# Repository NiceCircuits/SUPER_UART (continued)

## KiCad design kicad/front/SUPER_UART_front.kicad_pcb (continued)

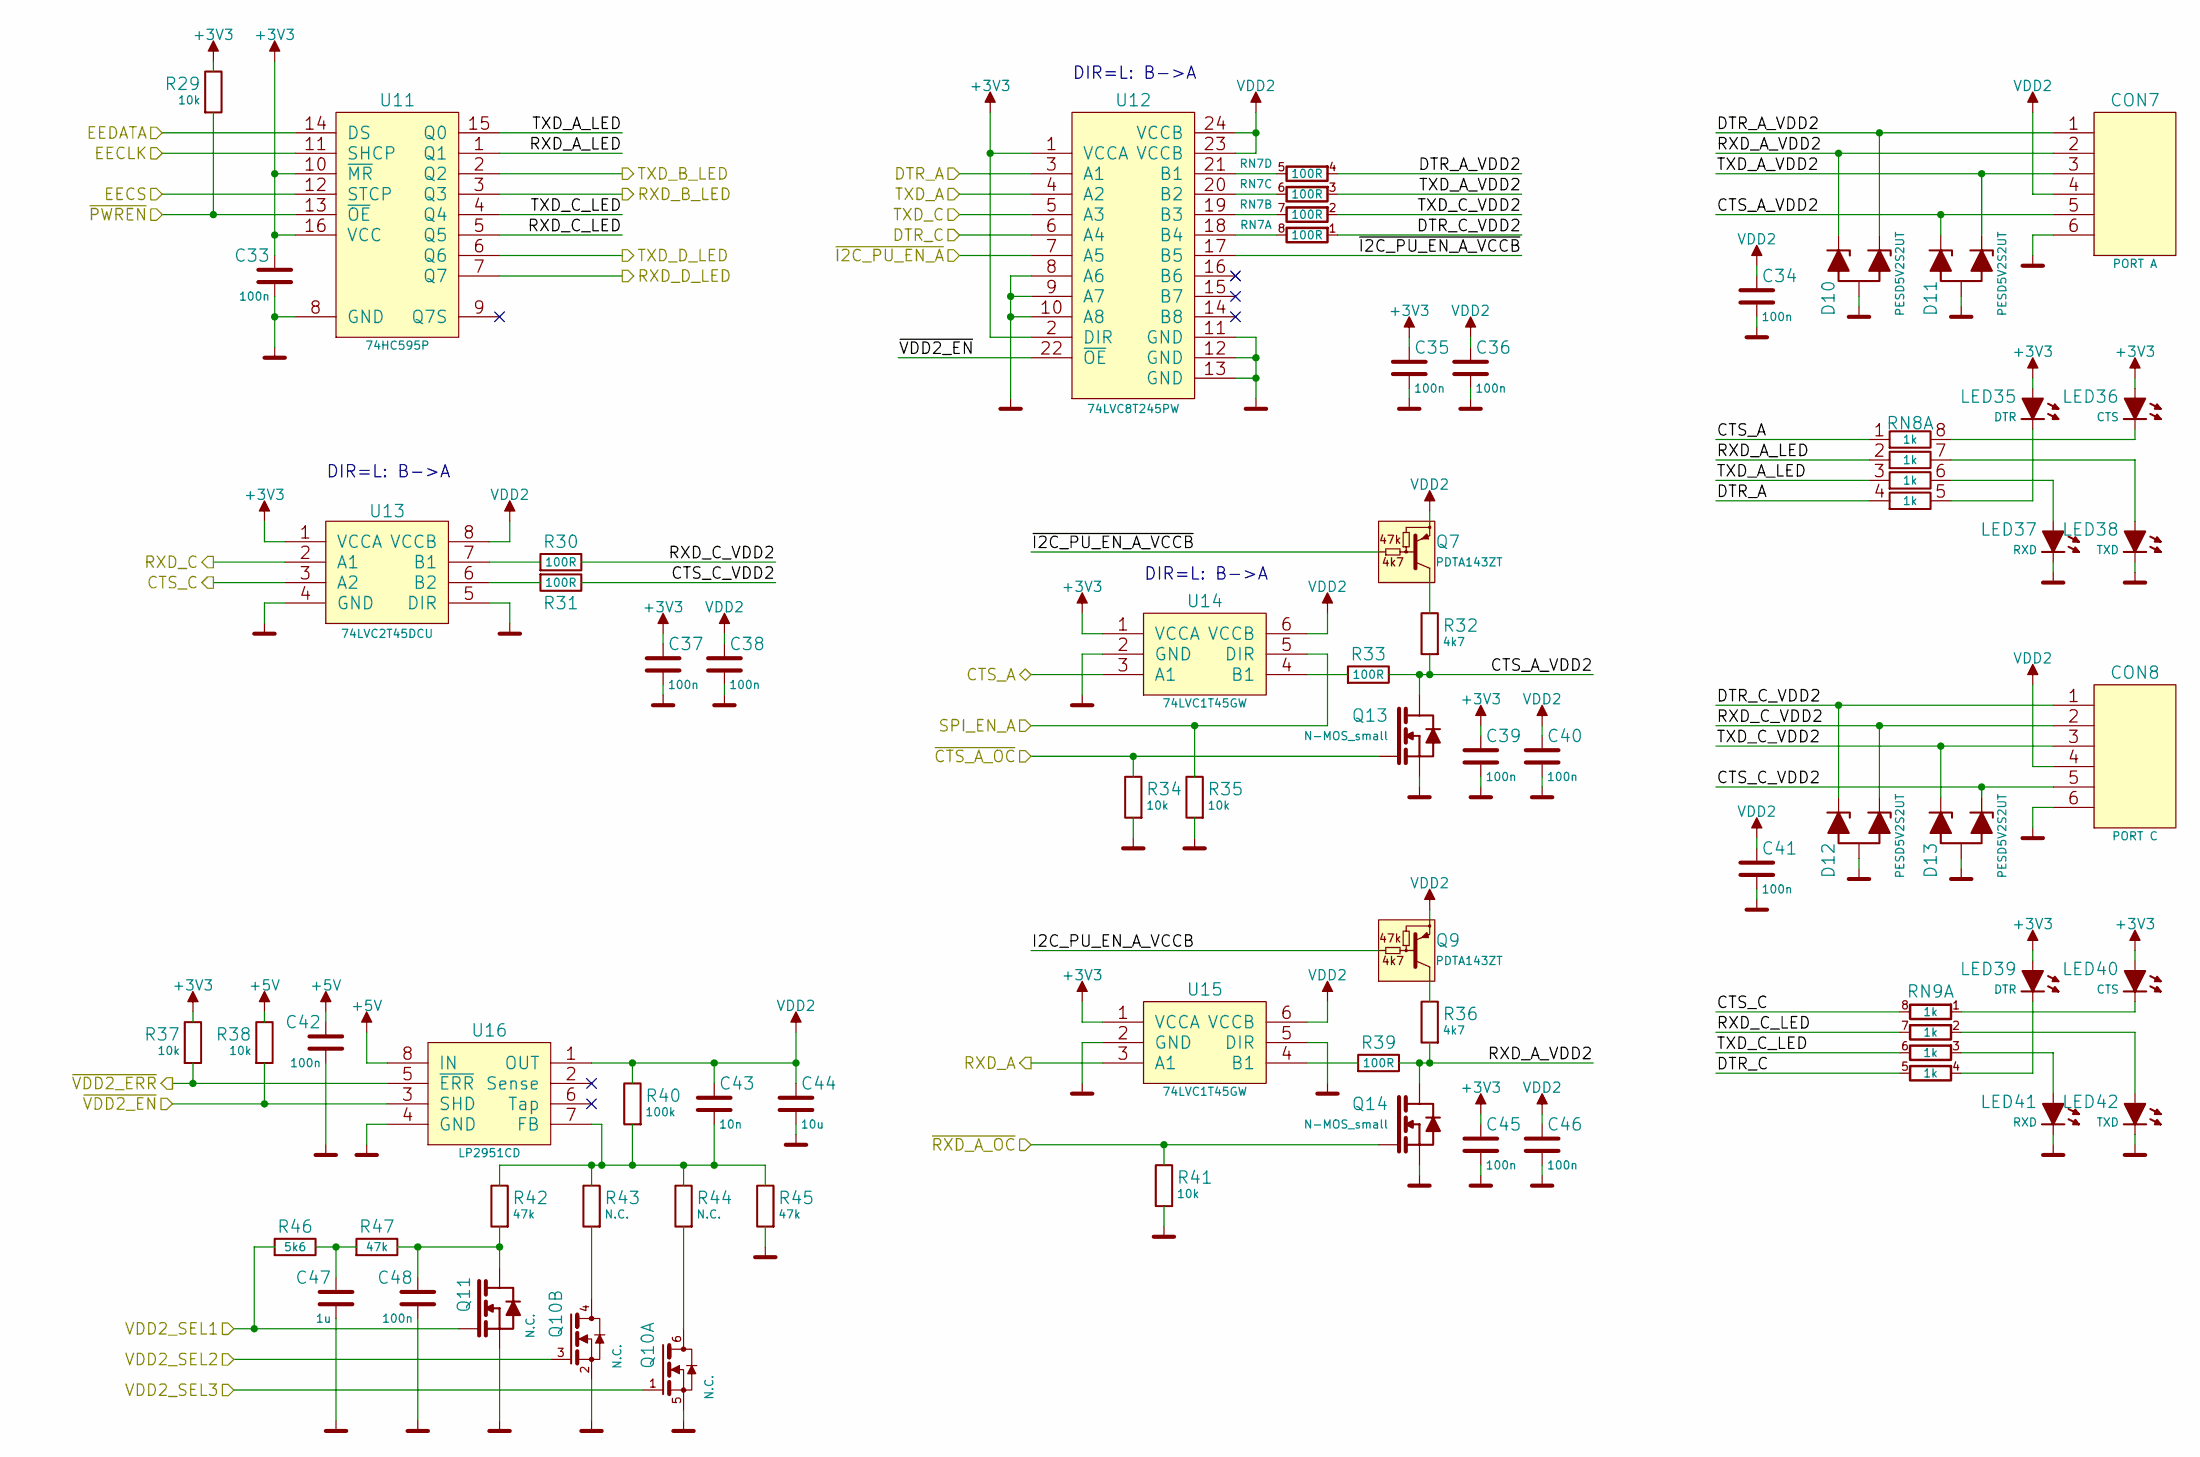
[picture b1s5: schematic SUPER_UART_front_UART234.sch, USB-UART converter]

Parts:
C33, C34, C35, C36, C37, C38, C39, C40, C41, C42, C45, C46, C48: 100n; 0603_N
C43: 10n; 0603_N
C44: 10u; 0805_N
C47: 1u; 0603_N
CON7: PORT A; NIGINI_NCDW-06
CON8: PORT C; NIGINI_NCDW-06
D10, D11, D12, D13: PESD5V2S2UT; SOT23-3_N
LED35, LED39: DTR; 0805D
LED36, LED40: CTS; 0805D
LED37, LED41: RXD; 0805D
LED38, LED42: TXD; 0805D
Q7, Q9: PDTA143ZT; SOT23-3_N
Q10: N.C.; SC70-6_N
Q11: N.C.; SOT23-3_N
Q13, Q14: N-MOS_small; SOT23-3_N
R29, R34, R35, R37, R38, R41: 10k; 0603_R_N
R30, R31, R33, R39: 100R; 0603_R_N
R32, R36: 4k7; 0603_R_N
R40: 100k; 0603_R_N
R42, R45, R47: 47k; 0603_R_N
R43, R44: N.C.; 0603_R_N
R46: 5k6; 0603_R_N
RN7: 100R; 4x0603_N
RN8, RN9: 1k; 4x0603_N
U11: 74HC595P; TSSOP-16_N
U12: 74LVC8T245PW; TI_TSSOP-24_N
U13: 74LVC2T45DCU; TI_VSSOP-8_N
U14, U15: 74LVC1T45GW; SC70-6_N
U16: LP2951CD; SOIC-8_N

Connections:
+3V3: C33.1, C35.1, C37.1, C39.1, C45.1, LED35.2 (C), LED36.2 (C), LED39.2 (C), LED40.2 (C), R29.2, R37.2, U11.10 (~MR), U11.16 (VCC), U12.1 (VCCA), U12.2 (DIR), U13.1 (VCCA), U14.1 (VCCA), U15.1 (VCCA); also elsewhere on the board
+5V: C42.1, R38.2, U16.8 (IN); also elsewhere on the board
/CTS_A: RN8.1, U14.3 (A1); also elsewhere on the board
/CTS_C: RN9.8, U13.3 (A2); also elsewhere on the board
/DTR_A: RN8.4 (1), U12.3 (A1); also elsewhere on the board
/DTR_C: RN9.5, U12.6 (A4); also elsewhere on the board
/EECLK: U11.11 (SHCP); also elsewhere on the board
/EECS: U11.12 (STCP); also elsewhere on the board
/EEDATA: U11.14 (DS); also elsewhere on the board
/RXD_A: U15.3 (A1); also elsewhere on the board
/RXD_C: U13.2 (A1); also elsewhere on the board
/SUPER_UART_front_UART1/RXD_B_LED: U11.3 (Q3); also elsewhere on the board
/SUPER_UART_front_UART1/RXD_D_LED: U11.7 (Q7); also elsewhere on the board
/SUPER_UART_front_UART1/TXD_B_LED: U11.2 (Q2); also elsewhere on the board
/SUPER_UART_front_UART1/TXD_D_LED: U11.6 (Q6); also elsewhere on the board
/SUPER_UART_front_UART234/CTS_A_VDD2: CON7.5, D11.1 (C1), Q13.3 (D), R32.1, R33.2
/SUPER_UART_front_UART234/CTS_C_VDD2: CON8.5, D13.2 (C2), R31.2
/SUPER_UART_front_UART234/DTR_A_VDD2: CON7.1, D10.2 (C2), RN7.4
/SUPER_UART_front_UART234/DTR_C_VDD2: CON8.1, D12.1 (C1), RN7.1
/SUPER_UART_front_UART234/I2C_PU_EN_A: U12.7 (A5); also elsewhere on the board
/SUPER_UART_front_UART234/RXD_A_LED: RN8.2 (1), U11.1 (Q1)
/SUPER_UART_front_UART234/RXD_A_VDD2: CON7.2, D10.1 (C1), Q14.3 (D), R36.1, R39.2
/SUPER_UART_front_UART234/RXD_C_LED: RN9.7, U11.5 (Q5)
/SUPER_UART_front_UART234/RXD_C_VDD2: CON8.2, D12.2 (C2), R30.2
/SUPER_UART_front_UART234/SPI_EN_A: R35.2, U14.5 (DIR); also elsewhere on the board
/SUPER_UART_front_UART234/TXD_A_LED: RN8.3 (1), U11.15 (Q0)
/SUPER_UART_front_UART234/TXD_A_VDD2: CON7.3, D11.2 (C2), RN7.3
/SUPER_UART_front_UART234/TXD_C_LED: RN9.6, U11.4 (Q4)
/SUPER_UART_front_UART234/TXD_C_VDD2: CON8.3, D13.1 (C1), RN7.2
/SUPER_UART_front_UART234/VDD2_SEL1: Q11.1 (G), R46.1; also elsewhere on the board
/SUPER_UART_front_UART234/VDD2_SEL2: Q10.3 (G); also elsewhere on the board
/SUPER_UART_front_UART234/VDD2_SEL3: Q10.1 (G); also elsewhere on the board
/SUPER_UART_front_UART234/~VDD2_EN: R38.1, U12.22 (~OE), U16.3 (SHD); also elsewhere on the board
/SUPER_UART_front_UART234/~VDD2_ERR: R37.1, U16.5 (~ERR); also elsewhere on the board
/TXD_A: U12.4 (A2); also elsewhere on the board
/TXD_C: U12.5 (A3); also elsewhere on the board
/~CTS_A_OC: Q13.1 (G), R34.2; also elsewhere on the board
/~PWREN: R29.1, U11.13 (~OE); also elsewhere on the board
/~RXD_A_OC: Q14.1 (G), R41.2; also elsewhere on the board
GND: C33.2, C34.2, C35.2, C36.2, C37.2, C38.2, C39.2, C40.2, C41.2, C42.2, C44.2, C45.2, C46.2, C47.2, C48.2, CON7.6, CON8.6, D10.3 (A), D11.3 (A), D12.3 (A), D13.3 (A), LED37.1 (A), LED38.1 (A), LED41.1 (A), LED42.1 (A), Q10.2 (S), Q10.5 (S), Q11.2 (S), Q13.2 (S), Q14.2 (S), R34.1, R35.1, R41.1, R45.1, U11.8 (GND), U12.8 (A6), U12.9 (A7), U12.10 (A8), U12.11 (GND), U12.12 (GND), U12.13 (GND), U13.4 (GND), U13.5 (DIR), U14.2 (GND), U15.2 (GND), U15.5 (DIR), U16.4 (GND); also elsewhere on the board
unnamed: C43.2, R40.1, R42.2, R43.2, R44.2, R45.2, U16.7 (FB)
unnamed: C47.1, R46.2, R47.1
unnamed: C48.1, Q11.3 (D), R42.1, R47.2
unnamed: LED35.1 (A), RN8.5 (2)
unnamed: LED36.1 (A), RN8.8 (2)
unnamed: LED37.2 (C), RN8.6 (2)
unnamed: LED38.2 (C), RN8.7 (2)
unnamed: LED39.1 (A), RN9.4
unnamed: LED40.1 (A), RN9.1
unnamed: LED41.2 (C), RN9.3
unnamed: LED42.2 (C), RN9.2
unnamed: Q7.3 (C), R32.2
unnamed: Q9.3 (C), R36.2
unnamed: Q10.4 (D), R43.1
unnamed: Q10.6 (D), R44.1
unnamed: R30.1, U13.7 (B1)
unnamed: R31.1, U13.6 (B2)
unnamed: R33.1, U14.4 (B1)
unnamed: R39.1, U15.4 (B1)
unnamed: RN7.5, U12.21 (B1)
unnamed: RN7.6, U12.20 (B2)
unnamed: RN7.7, U12.19 (B3)
unnamed: RN7.8, U12.18 (B4)
VDD2: C34.1, C36.1, C38.1, C40.1, C41.1, C43.1, C44.1, C46.1, CON7.4, CON8.4, Q7.2 (E), Q9.2 (E), R40.2, U12.23 (VCCB), U12.24 (VCCB), U13.8 (VCCB), U14.6 (VCCB), U15.6 (VCCB), U16.1 (OUT); also elsewhere on the board

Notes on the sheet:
DIR=L: B->A

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
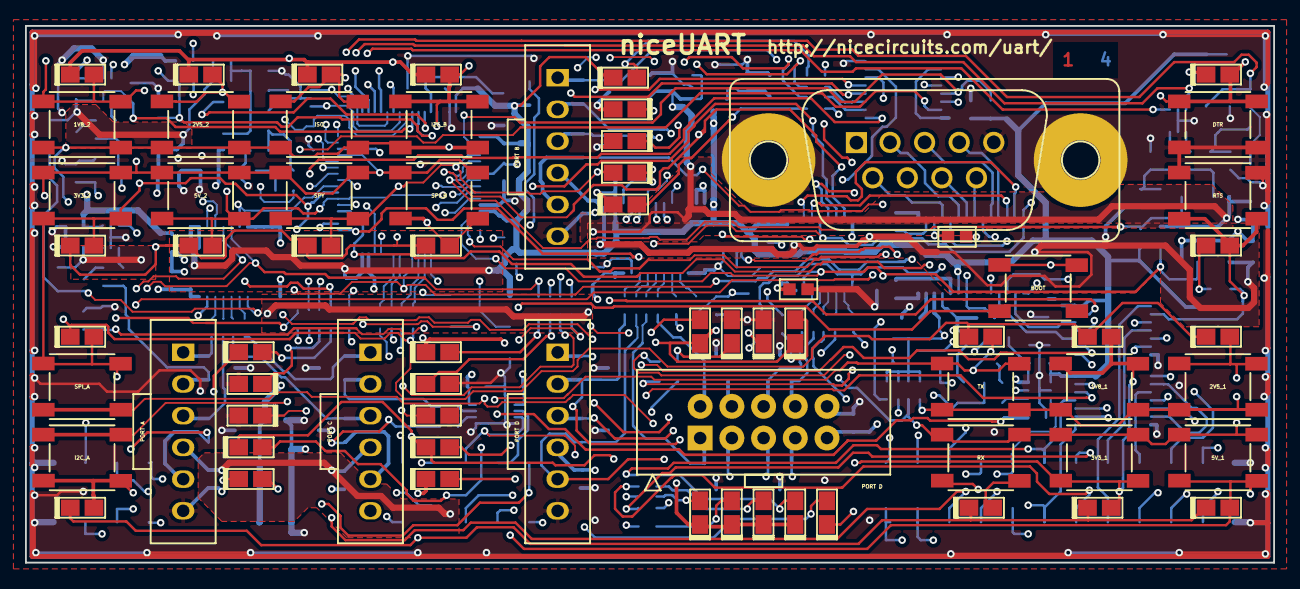
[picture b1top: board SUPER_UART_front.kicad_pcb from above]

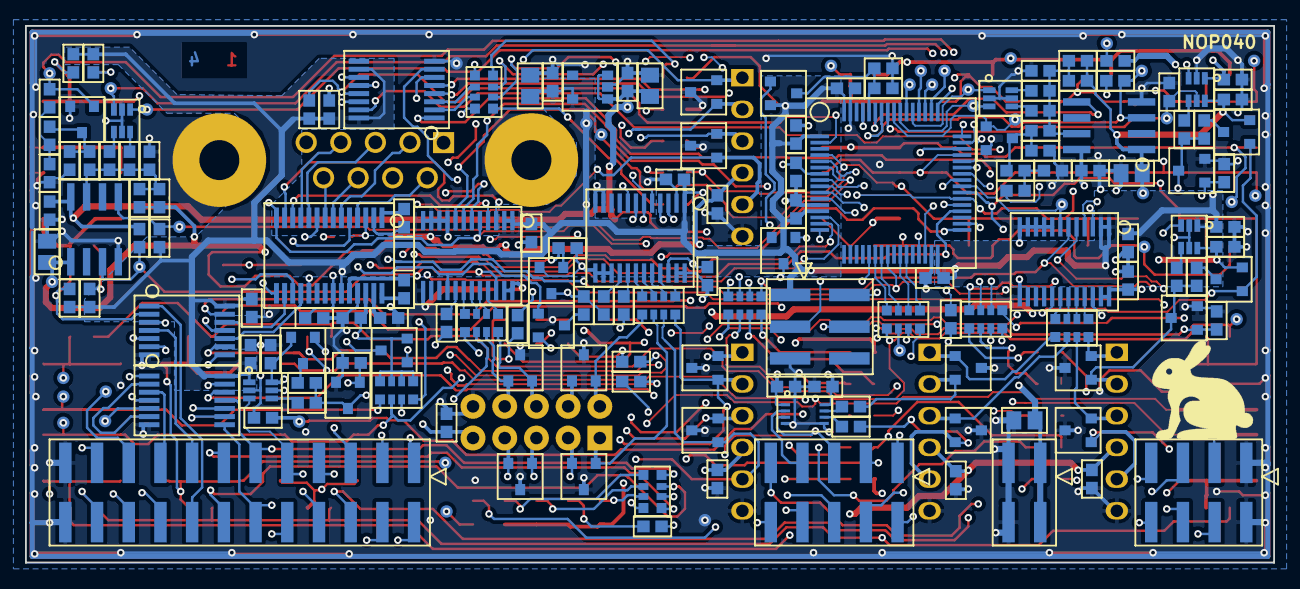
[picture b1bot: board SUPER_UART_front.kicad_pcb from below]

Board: 4 copper layers, 100.0 x 43.0 mm, 260 parts (188 on the bottom side), 201 nets.

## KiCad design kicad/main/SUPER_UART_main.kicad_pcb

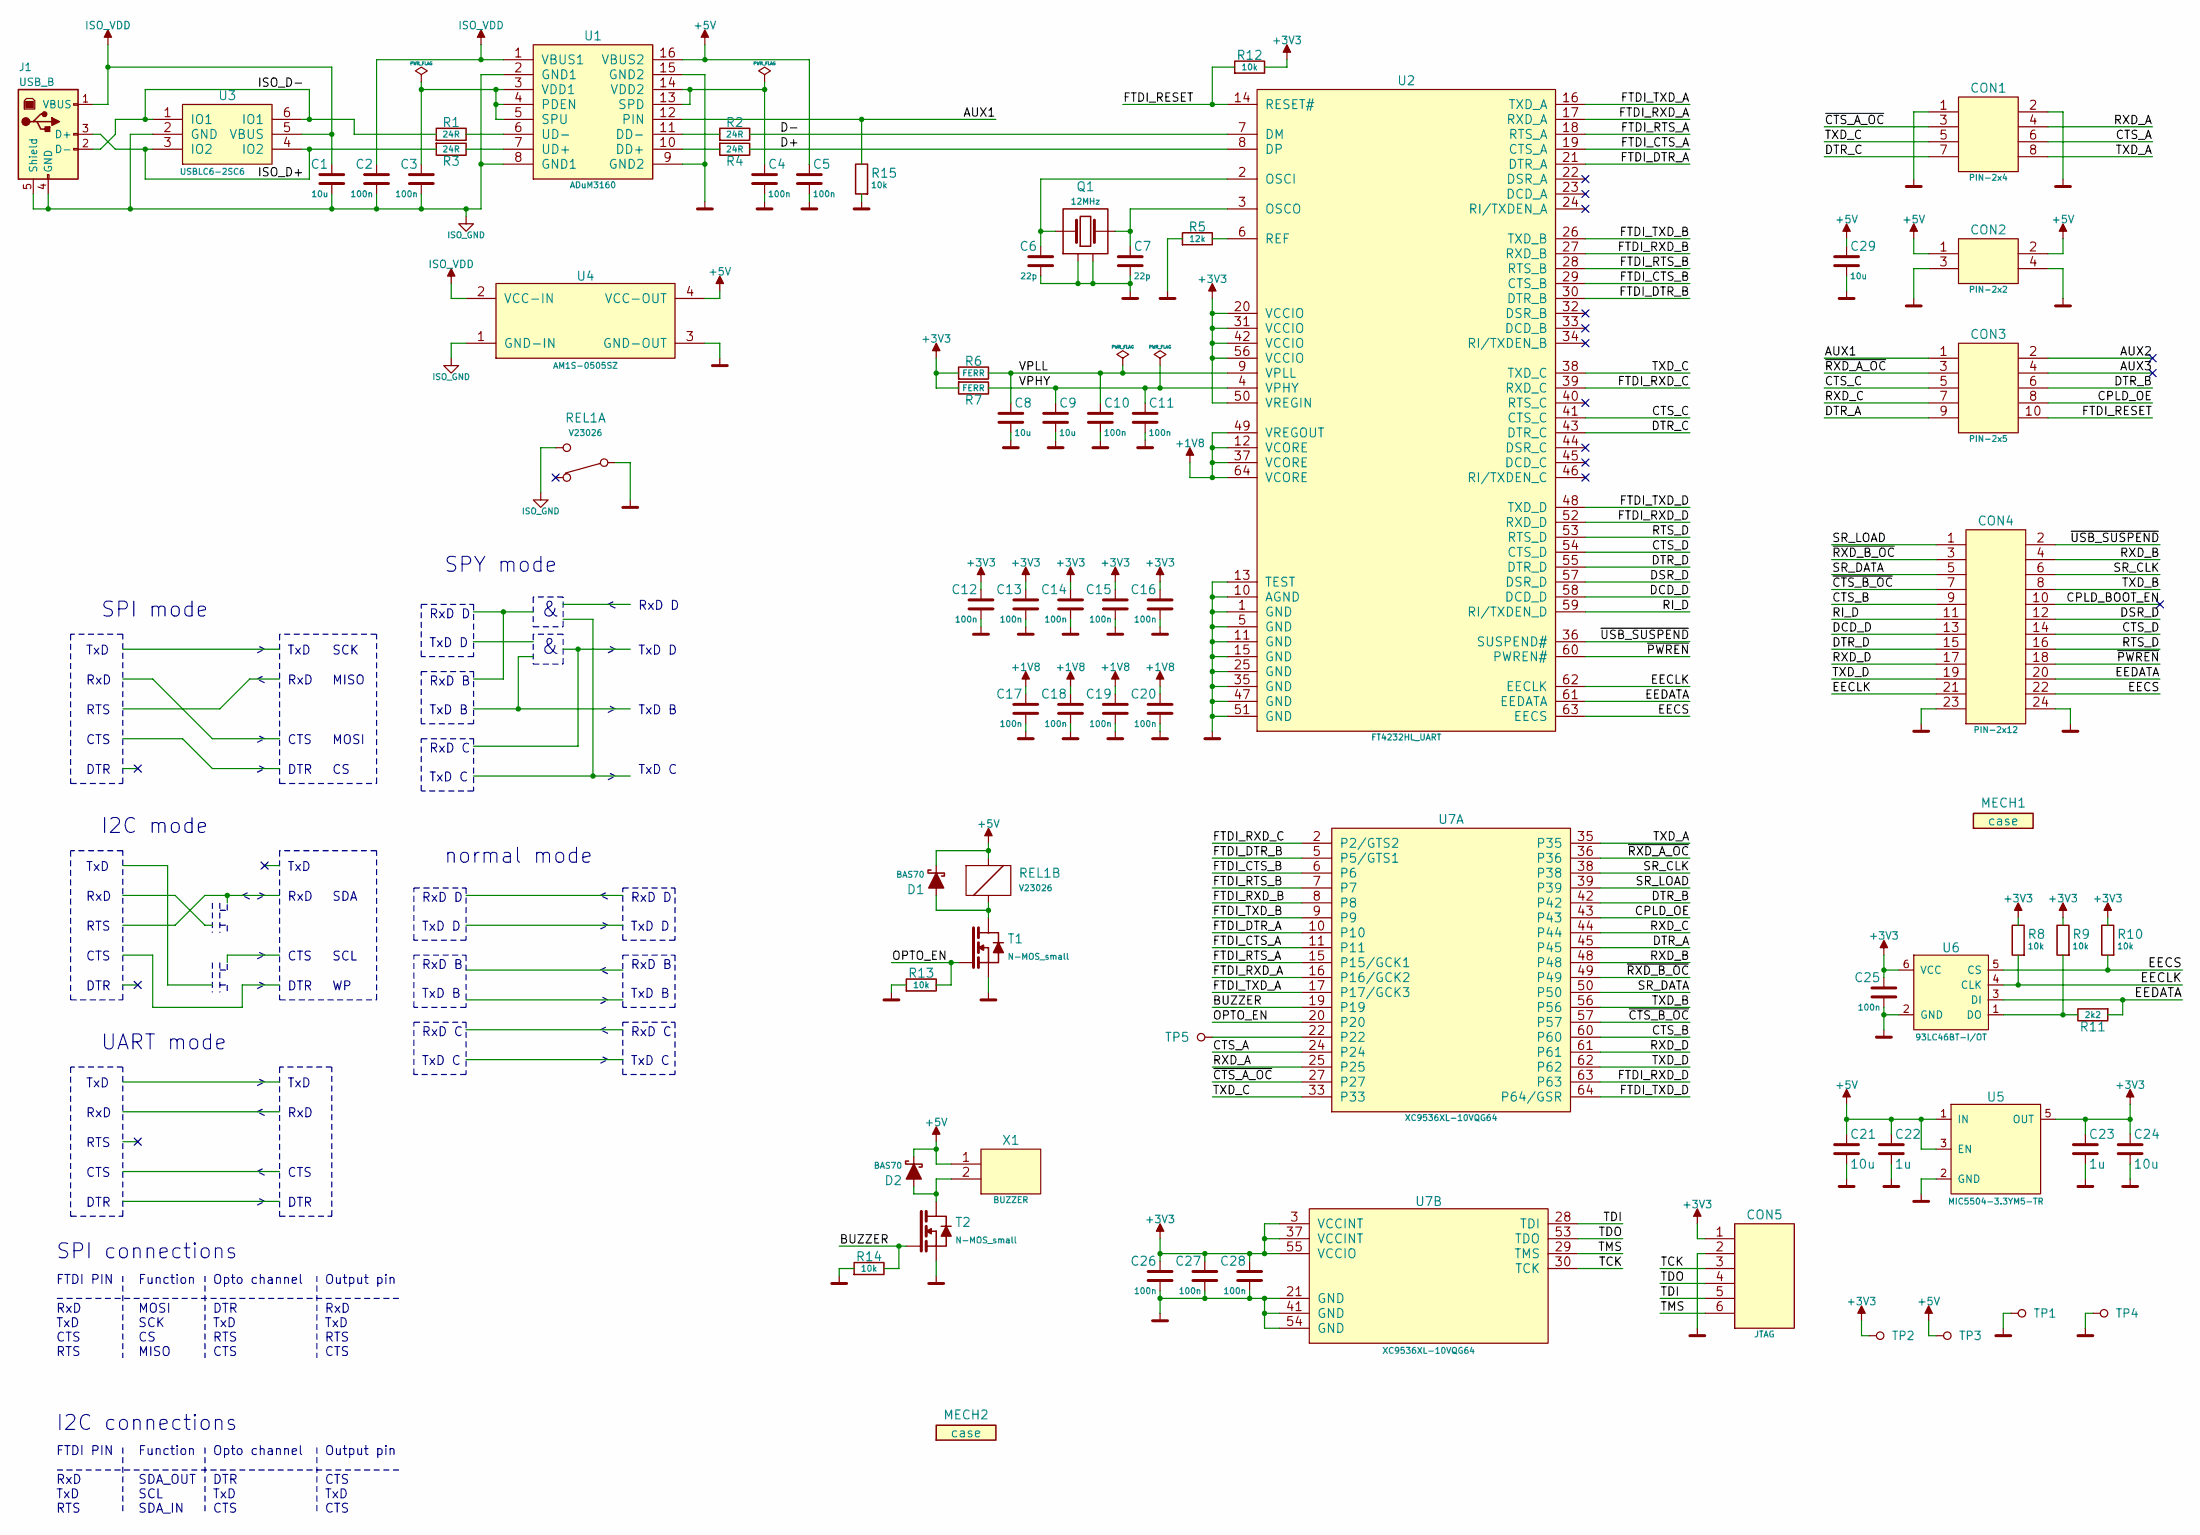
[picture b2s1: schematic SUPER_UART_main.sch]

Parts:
C1, C8, C9, C21, C24, C29: 10u; 0805_N
C2, C3, C4, C5, C10, C11, C12, C13, C14, C15, C16, C17, C18, C19, C20, C25, C26, C27, C28: 100n; 0603_N
C6, C7: 22p; 0603_N
C22, C23: 1u; 0603_N
CON1: PIN-2x4; PIN-2x4_F_angled_N
CON2: PIN-2x2; PIN-2x2_F_angled_N
CON3: PIN-2x5; PIN-2x5_F_angled_N
CON4: PIN-2x12; PIN-2x12_F_angled_N
CON5: JTAG; PIN-1x6_N
D1, D2: BAS70; SOT23-3_N
J1: USB_B
MECH1: case; dummy
MECH2: case; frog
Q1: 12MHz; XT3.2x2.5_N
R1, R2, R3, R4: 24R; 0603_R_N
R5: 12k; 0603_R_N
R6, R7: FERR; 0603_R_N
R8, R9, R10, R12, R13, R14, R15: 10k; 0603_R_N
R11: 2k2; 0603_R_N
REL1: V23026
T1, T2: N-MOS_small; SOT23-3_N
TP1, TP2, TP3, TP4, TP5: Testpoint; TP_1mm
U1: ADuM3160; SOIC-16_N
U2: FT4232HL_UART; FTDI_LQFP64_M
U3: USBLC6-2SC6; SOT23-6_N
U4: AM1S-0505SZ; AM1S-Z_N
U5: MIC5504-3.3YM5-TR; SOT23-5_N
U6: 93LC46BT-I/OT; SOT23-6_N
U7: XC9536XL-10VQG64; Xilinx_VQFP64_M
X1: BUZZER; buzzer_12x9.0

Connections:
+1V8: C17.1, C18.1, C19.1, C20.1, U2.12 (VCORE), U2.37 (VCORE), U2.49 (VREGOUT), U2.64 (VCORE)
+3V3: C12.1, C13.1, C14.1, C15.1, C16.1, C23.1, C24.1, C25.1, C26.1, C27.1, C28.1, CON5.1, R6.1, R7.1, R8.2, R9.2, R10.2, R12.2, TP2.1, U2.20 (VCCIO), U2.31 (VCCIO), U2.42 (VCCIO), U2.50 (VREGIN), U2.56 (VCCIO), U5.5 (OUT), U6.6 (VCC), U7.3 (VCCINT), U7.37 (VCCINT), U7.55 (VCCIO)
+5V: C5.1, C21.1, C22.1, C29.1, CON2.1, CON2.2, D1.3 (A), D2.3 (A), REL1.C1 (COIL1), TP3.1, U1.16 (VBUS2), U4.4 (VCC-OUT), U5.1 (IN), U5.3 (EN), X1.1
/AUX1: CON3.1, R15.2, U1.12 (PIN)
/BUZZER: R14.2, T2.1 (G), U7.19
/CPLD_OE: CON3.8, U7.43
/CTS_A: CON1.6, U7.24
/CTS_B: CON4.9, U7.60
/CTS_C: CON3.5, U2.41 (CTS_C)
/CTS_D: CON4.14, U2.54 (CTS_D)
/D+: R4.2, U2.8 (DP)
/D-: R2.2, U2.7 (DM)
/DCD_D: CON4.13, U2.58 (DCD_D)
/DSR_D: CON4.12, U2.57 (DSR_D)
/DTR_A: CON3.9, U7.45
/DTR_B: CON3.6, U7.42
/DTR_C: CON1.7, U2.43 (DTR_C)
/DTR_D: CON4.15, U2.55 (DTR_D)
/EECLK: CON4.21, R8.1, U2.62 (EECLK), U6.4 (CLK)
/EECS: CON4.22, R10.1, U2.63 (EECS), U6.5 (CS)
/EEDATA: CON4.20, R11.1, U2.61 (EEDATA), U6.3 (DI)
/FTDI_CTS_A: U2.19 (CTS_A), U7.11
/FTDI_CTS_B: U2.29 (CTS_B), U7.6
/FTDI_DTR_A: U2.21 (DTR_A), U7.10
/FTDI_DTR_B: U2.30 (DTR_B), U7.5 (P5/GTS1)
/FTDI_RESET: CON3.10, R12.1, U2.14 (RESET#)
/FTDI_RTS_A: U2.18 (RTS_A), U7.15 (P15/GCK1)
/FTDI_RTS_B: U2.28 (RTS_B), U7.7
/FTDI_RXD_A: U2.17 (RXD_A), U7.16 (P16/GCK2)
/FTDI_RXD_B: U2.27 (RXD_B), U7.8
/FTDI_RXD_C: U2.39 (RXD_C), U7.2 (P2/GTS2)
/FTDI_RXD_D: U2.52 (RXD_D), U7.63
/FTDI_TXD_A: U2.16 (TXD_A), U7.17 (P17/GCK3)
/FTDI_TXD_B: U2.26 (TXD_B), U7.9
/FTDI_TXD_D: U2.48 (TXD_D), U7.64 (P64/GSR)
/ISO_D+: J1.3 (D+), R3.1, U3.3 (IO2), U3.4 (IO2)
/ISO_D-: J1.2 (D-), R1.1, U3.1 (IO1), U3.6 (IO1)
/OPTO_EN: R13.2, T1.1 (G), U7.20
/RI_D: CON4.11, U2.59 (RI/TXDEN_D)
/RTS_D: CON4.16, U2.53 (RTS_D)
/RXD_A: CON1.4, U7.25
/RXD_B: CON4.4, U7.48
/RXD_C: CON3.7, U7.44
/RXD_D: CON4.17, U7.61
/SR_CLK: CON4.6, U7.38
/SR_DATA: CON4.5, U7.50
/SR_LOAD: CON4.1, U7.39
/TCK: CON5.3, U7.30 (TCK)
/TDI: CON5.5, U7.28 (TDI)
/TDO: CON5.4, U7.53 (TDO)
/TMS: CON5.6, U7.29 (TMS)
/TXD_A: CON1.8, U7.35
/TXD_B: CON4.8, U7.56
/TXD_C: CON1.5, U2.38 (TXD_C), U7.33
/TXD_D: CON4.19, U7.62
/VPHY: C9.1, C11.1, R7.2, U2.4 (VPHY)
/VPLL: C8.1, C10.1, R6.2, U2.9 (VPLL)
/~CTS_A_OC: CON1.3, U7.27
/~CTS_B_OC: CON4.7, U7.57
/~PWREN: CON4.18, U2.60 (PWREN#)
/~RXD_A_OC: CON3.3, U7.36
/~RXD_B_OC: CON4.3, U7.49
/~USB_SUSPEND: CON4.2, U2.36 (SUSPEND#)
GND: C4.2, C5.2, C6.2, C7.2, C8.2, C9.2, C10.2, C11.2, C12.2, C13.2, C14.2, C15.2, C16.2, C17.2, C18.2, C19.2, C20.2, C21.2, C22.2, C23.2, C24.2, C25.2, C26.2, C27.2, C28.2, C29.2, CON1.1, CON1.2, CON2.3, CON2.4, CON4.23, CON4.24, CON5.2, Q1.2, Q1.4, R5.1, R13.1, R14.1, R15.1, REL1.COM, T1.2 (S), T2.2 (S), TP1.1, TP4.1, U1.9 (GND2), U1.15 (GND2), U2.1 (GND), U2.5 (GND), U2.10 (AGND), U2.11 (GND), U2.13 (TEST), U2.15 (GND), U2.25 (GND), U2.35 (GND), U2.47 (GND), U2.51 (GND), U4.3 (GND-OUT), U5.2 (GND), U6.2 (GND), U7.21 (GND), U7.41 (GND), U7.54 (GND)
ISO_GND: C1.2, C2.2, C3.2, J1.4 (GND), J1.5 (Shield), REL1.NO, U1.2 (GND1), U1.8 (GND1), U3.2 (GND), U4.1 (GND-IN)
ISO_VDD: C1.1, C2.1, J1.1 (VBUS), U1.1 (VBUS1), U3.5 (VBUS), U4.2 (VCC-IN)
unnamed: C3.1, U1.3 (VDD1), U1.4 (PDEN), U1.5 (SPU)
unnamed: C4.1, U1.13 (SPD), U1.14 (VDD2)
unnamed: C6.1, Q1.1, U2.2 (OSCI)
unnamed: C7.1, Q1.3, U2.3 (OSCO)
unnamed: D1.1 (C), REL1.C2 (COIL2), T1.3 (D)
unnamed: D2.1 (C), T2.3 (D), X1.2
unnamed: R1.2, U1.6 (UD-)
unnamed: R2.1, U1.11 (DD-)
unnamed: R3.2, U1.7 (UD+)
unnamed: R4.1, U1.10 (DD+)
unnamed: R5.2, U2.6 (REF)
unnamed: R9.1, R11.2, U6.1 (DO)
unnamed: TP5.1, U7.22

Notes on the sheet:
SPY mode
RxD D TxD D
RxD B TxD B
RxD C TxD C
RxD D
TxD D
normal mode
SPI mode
TxD
RxD
RTS
CTS
DTR
SCK
MISO
MOSI
I2C mode
SDA
SCL
UART mode
TxD B
TxD C
FTDI PIN RxD TxD CTS RTS
Function MOSI SCK CS MISO
Opto channel DTR TxD RTS CTS
Output pin RxD TxD RTS CTS
SPI connections
FTDI PIN RxD TxD RTS
Function SDA_OUT SCL SDA_IN
Opto channel DTR TxD CTS
Output pin CTS TxD CTS
I2C connections

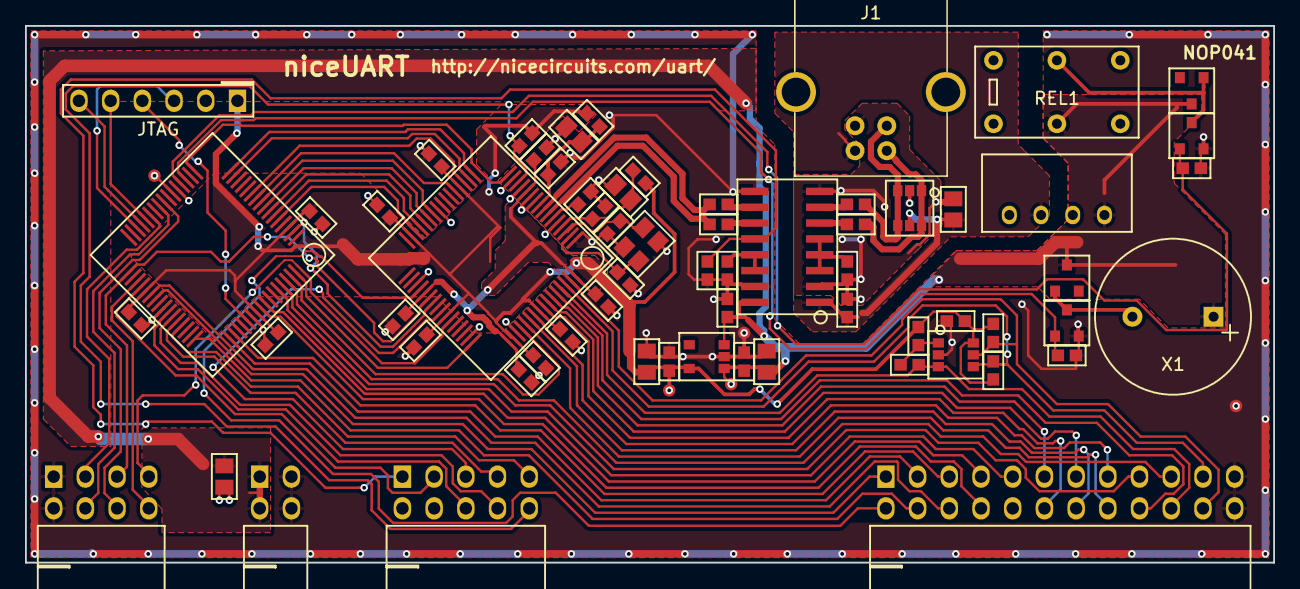
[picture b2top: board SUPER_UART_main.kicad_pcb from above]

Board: 2 copper layers, 100.0 x 43.0 mm, 71 parts (1 on the bottom side), 79 nets.

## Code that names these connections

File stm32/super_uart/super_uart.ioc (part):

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Mcu.Name=STM32F030R8Tx
Mcu.Package=LQFP64
Mcu.UserName=STM32F030R8Tx
PA0.GPIOParameters=GPIO_Speed,PinState,GPIO_PuPd,GPIO_Label,GPIO_ModeDefaultOutputPP
PA0.GPIO_Label=N_VDD1_EN
PA0.GPIO_ModeDefaultOutputPP=GPIO_MODE_OUTPUT_PP
PA0.GPIO_PuPd=GPIO_NOPULL
PA0.GPIO_Speed=GPIO_SPEED_FREQ_LOW
PA0.PinState=GPIO_PIN_SET
PA0.Signal=GPIO_Output
PA1.GPIOParameters=GPIO_PuPd,GPIO_Label
PA1.GPIO_Label=SW3
PA1.GPIO_PuPd=GPIO_PULLUP
PA1.Signal=GPIO_Input
PA10.GPIOParameters=GPIO_PuPd,GPIO_Label
PA10.GPIO_Label=RXD
PA10.GPIO_PuPd=GPIO_PULLUP
PA10.Signal=GPIO_Input
PA11.GPIOParameters=GPIO_Label
PA11.GPIO_Label=VDD1_SEL1
PA11.Signal=S_TIM1_CH4
PA12.GPIOParameters=GPIO_PuPd,GPIO_Label
PA12.GPIO_Label=SW4
PA12.GPIO_PuPd=GPIO_PULLUP
PA12.Signal=GPIO_Input
PA13.Mode=Serial_Wire
PA13.Signal=SYS_SWDIO
PA14.Mode=Serial_Wire
PA14.Signal=SYS_SWCLK
PA2.GPIOParameters=GPIO_Speed,PinState,GPIO_PuPd,GPIO_Label,GPIO_ModeDefaultOutputPP
PA2.GPIO_Label=N_FTDI_RESET
PA2.GPIO_ModeDefaultOutputPP=GPIO_MODE_OUTPUT_PP
PA2.GPIO_PuPd=GPIO_NOPULL
PA2.GPIO_Speed=GPIO_SPEED_FREQ_LOW
PA2.PinState=GPIO_PIN_SET
PA2.Signal=GPIO_Output
PA6.GPIOParameters=GPIO_Speed,PinState,GPIO_PuPd,GPIO_Label,GPIO_ModeDefaultOutputPP
PA6.GPIO_Label=LED1
PA6.GPIO_ModeDefaultOutputPP=GPIO_MODE_OUTPUT_PP
PA6.GPIO_PuPd=GPIO_NOPULL
PA6.GPIO_Speed=GPIO_SPEED_FREQ_LOW
PA6.PinState=GPIO_PIN_RESET
PA6.Signal=GPIO_Output
PA7.GPIOParameters=GPIO_Speed,PinState,GPIO_PuPd,GPIO_Label,GPIO_ModeDefaultOutputPP
PA7.GPIO_Label=LED2
PA7.GPIO_ModeDefaultOutputPP=GPIO_MODE_OUTPUT_PP
PA7.GPIO_PuPd=GPIO_NOPULL
PA7.GPIO_Speed=GPIO_SPEED_FREQ_LOW
PA7.PinState=GPIO_PIN_RESET
PA7.Signal=GPIO_Output
PA8.GPIOParameters=GPIO_Speed,PinState,GPIO_PuPd,GPIO_Label,GPIO_ModeDefaultOutputPP
PA8.GPIO_Label=LED5
PA8.GPIO_ModeDefaultOutputPP=GPIO_MODE_OUTPUT_PP
PA8.GPIO_PuPd=GPIO_NOPULL
PA8.GPIO_Speed=GPIO_SPEED_FREQ_LOW
PA8.PinState=GPIO_PIN_RESET
PA8.Signal=GPIO_Output
PA9.GPIOParameters=GPIO_Speed,PinState,GPIO_PuPd,GPIO_Label,GPIO_ModeDefaultOutputPP
PA9.GPIO_Label=TXD
PA9.GPIO_ModeDefaultOutputPP=GPIO_MODE_OUTPUT_PP
PA9.GPIO_PuPd=GPIO_NOPULL
PA9.GPIO_Speed=GPIO_SPEED_FREQ_LOW
PA9.PinState=GPIO_PIN_SET
PA9.Signal=GPIO_Output
PB0.GPIOParameters=GPIO_Speed,PinState,GPIO_PuPd,GPIO_Label,GPIO_ModeDefaultOutputPP
PB0.GPIO_Label=LED3
PB0.GPIO_ModeDefaultOutputPP=GPIO_MODE_OUTPUT_PP
PB0.GPIO_PuPd=GPIO_NOPULL
PB0.GPIO_Speed=GPIO_SPEED_FREQ_LOW
PB0.PinState=GPIO_PIN_RESET
PB0.Signal=GPIO_Output
PB1.GPIOParameters=GPIO_Speed,PinState,GPIO_PuPd,GPIO_Label,GPIO_ModeDefaultOutputPP
PB1.GPIO_Label=LED4
PB1.GPIO_ModeDefaultOutputPP=GPIO_MODE_OUTPUT_PP
PB1.GPIO_PuPd=GPIO_NOPULL
PB1.GPIO_Speed=GPIO_SPEED_FREQ_LOW
PB1.PinState=GPIO_PIN_RESET
PB1.Signal=GPIO_Output
PB10.GPIOParameters=PinState,GPIO_Label
PB10.GPIO_Label=N_ENUMERATE
PB10.PinState=GPIO_PIN_SET
PB10.Signal=GPIO_Output
PB12.GPIOParameters=GPIO_Speed,PinState,GPIO_PuPd,GPIO_Label,GPIO_ModeDefaultOutputPP
PB12.GPIO_Label=SR_LOAD
PB12.GPIO_ModeDefaultOutputPP=GPIO_MODE_OUTPUT_PP
PB12.GPIO_PuPd=GPIO_NOPULL
PB12.GPIO_Speed=GPIO_SPEED_FREQ_LOW
PB12.PinState=GPIO_PIN_RESET
PB12.Signal=GPIO_Output
PB13.GPIOParameters=GPIO_Speed,GPIO_Label
PB13.GPIO_Label=SR_CLK
PB13.GPIO_Speed=GPIO_SPEED_FREQ_LOW
PB13.Mode=TX_Only_Simplex_Unidirect_Master
PB13.Signal=SPI2_SCK
PB15.GPIOParameters=GPIO_Speed,GPIO_Label
PB15.GPIO_Label=SR_DATA
PB15.GPIO_Speed=GPIO_SPEED_FREQ_LOW
PB15.Mode=TX_Only_Simplex_Unidirect_Master
PB15.Signal=SPI2_MOSI
PB3.GPIOParameters=GPIO_Speed,PinState,GPIO_PuPd,GPIO_Label,GPIO_ModeDefaultOutputPP
PB3.GPIO_Label=VDD2_SEL2
PB3.GPIO_ModeDefaultOutputPP=GPIO_MODE_OUTPUT_PP
PB3.GPIO_PuPd=GPIO_NOPULL
PB3.GPIO_Speed=GPIO_SPEED_FREQ_LOW
PB3.PinState=GPIO_PIN_RESET
PB3.Signal=GPIO_Output
PB4.GPIOParameters=GPIO_Label
PB4.GPIO_Label=VDD2_SEL1
PB4.Signal=S_TIM3_CH1
PB5.GPIOParameters=GPIO_Speed,PinState,GPIO_PuPd,GPIO_Label,GPIO_ModeDefaultOutputPP
PB5.GPIO_Label=SPI_EN_A
PB5.GPIO_ModeDefaultOutputPP=GPIO_MODE_OUTPUT_PP
PB5.GPIO_PuPd=GPIO_NOPULL
PB5.GPIO_Speed=GPIO_SPEED_FREQ_LOW
PB5.PinState=GPIO_PIN_RESET
PB5.Signal=GPIO_Output
PB6.GPIOParameters=GPIO_Speed,PinState,GPIO_PuPd,GPIO_Label,GPIO_ModeDefaultOutputPP
PB6.GPIO_Label=N_VDD2_EN
PB6.GPIO_ModeDefaultOutputPP=GPIO_MODE_OUTPUT_PP
PB6.GPIO_PuPd=GPIO_NOPULL
PB6.GPIO_Speed=GPIO_SPEED_FREQ_LOW
PB6.PinState=GPIO_PIN_SET
PB6.Signal=GPIO_Output
PB7.GPIOParameters=GPIO_PuPd,GPIO_Label
PB7.GPIO_Label=N_VDD2_ERR
PB7.GPIO_PuPd=GPIO_PULLUP
PB7.Signal=GPIO_Input
PB8.GPIOParameters=GPIO_Speed,PinState,GPIO_PuPd,GPIO_Label,GPIO_ModeDefaultOutputPP
PB8.GPIO_Label=COL1
PB8.GPIO_ModeDefaultOutputPP=GPIO_MODE_OUTPUT_PP
PB8.GPIO_PuPd=GPIO_NOPULL
PB8.GPIO_Speed=GPIO_SPEED_FREQ_LOW
PB8.PinState=GPIO_PIN_SET
PB8.Signal=GPIO_Output
PC0.GPIOParameters=GPIO_PuPd,GPIO_Label
PC0.GPIO_Label=SW2
PC0.GPIO_PuPd=GPIO_PULLUP
PC0.Signal=GPIO_Input
PC1.GPIOParameters=GPIO_Speed,PinState,GPIO_PuPd,GPIO_Label,GPIO_ModeDefaultOutputPP
PC1.GPIO_Label=CPLD_OE
PC1.GPIO_ModeDefaultOutputPP=GPIO_MODE_OUTPUT_PP
PC1.GPIO_PuPd=GPIO_NOPULL
PC1.GPIO_Speed=GPIO_SPEED_FREQ_LOW
PC1.PinState=GPIO_PIN_SET
PC1.Signal=GPIO_Output
PC12.GPIOParameters=GPIO_Speed,PinState,GPIO_PuPd,GPIO_Label,GPIO_ModeDefaultOutputPP
PC12.GPIO_Label=VDD2_SEL3
PC12.GPIO_ModeDefaultOutputPP=GPIO_MODE_OUTPUT_PP
PC12.GPIO_PuPd=GPIO_NOPULL
PC12.GPIO_Speed=GPIO_SPEED_FREQ_LOW
PC12.PinState=GPIO_PIN_RESET
PC12.Signal=GPIO_Output
PC13.GPIOParameters=GPIO_PuPd,GPIO_Label
PC13.GPIO_Label=N_PWREN
PC13.GPIO_PuPd=GPIO_PULLUP
PC13.Signal=GPIO_Input
PC15-OSC32_OUT.GPIOParameters=GPIO_Speed,PinState,GPIO_PuPd,GPIO_Label,GPIO_ModeDefaultOutputPP
PC15-OSC32_OUT.GPIO_Label=COL2
PC15-OSC32_OUT.GPIO_ModeDefaultOutputPP=GPIO_MODE_OUTPUT_PP
PC15-OSC32_OUT.GPIO_PuPd=GPIO_NOPULL
PC15-OSC32_OUT.GPIO_Speed=GPIO_SPEED_FREQ_LOW
PC15-OSC32_OUT.PinState=GPIO_PIN_SET
PC15-OSC32_OUT.Signal=GPIO_Output
PC2.GPIOParameters=GPIO_Speed,PinState,GPIO_PuPd,GPIO_Label,GPIO_ModeDefaultOutputPP
PC2.GPIO_Label=SPI_EN_B
PC2.GPIO_ModeDefaultOutputPP=GPIO_MODE_OUTPUT_PP
PC2.GPIO_PuPd=GPIO_NOPULL
PC2.GPIO_Speed=GPIO_SPEED_FREQ_LOW
PC2.PinState=GPIO_PIN_RESET
PC2.Signal=GPIO_Output
PC3.GPIOParameters=GPIO_PuPd,GPIO_Label
PC3.GPIO_Label=N_USB_SUSPEND
PC3.GPIO_PuPd=GPIO_PULLUP
PC3.Signal=GPIO_Input
PC4.GPIOParameters=GPIO_PuPd,GPIO_Label
PC4.GPIO_Label=SW1
PC4.GPIO_PuPd=GPIO_PULLUP
PC4.Signal=GPIO_Input
PC7.GPIOParameters=GPIO_Speed,PinState,GPIO_PuPd,GPIO_Label,GPIO_ModeDefaultOutputPP
PC7.GPIO_Label=COL3
PC7.GPIO_ModeDefaultOutputPP=GPIO_MODE_OUTPUT_PP
PC7.GPIO_PuPd=GPIO_NOPULL
PC7.GPIO_Speed=GPIO_SPEED_FREQ_LOW
PC7.PinState=GPIO_PIN_SET
PC7.Signal=GPIO_Output
PC8.GPIOParameters=GPIO_Speed,PinState,GPIO_PuPd,GPIO_Label,GPIO_ModeDefaultOutputPP
PC8.GPIO_Label=COL4
PC8.GPIO_ModeDefaultOutputPP=GPIO_MODE_OUTPUT_PP
PC8.GPIO_PuPd=GPIO_NOPULL
PC8.GPIO_Speed=GPIO_SPEED_FREQ_LOW
PC8.PinState=GPIO_PIN_SET
PC8.Signal=GPIO_Output
PC9.GPIOParameters=GPIO_Speed,PinState,GPIO_PuPd,GPIO_Label,GPIO_ModeDefaultOutputPP
PC9.GPIO_Label=N_I2C_PU_EN_A
PC9.GPIO_ModeDefaultOutputPP=GPIO_MODE_OUTPUT_PP
PC9.GPIO_PuPd=GPIO_NOPULL
PC9.GPIO_Speed=GPIO_SPEED_FREQ_LOW
PC9.PinState=GPIO_PIN_SET
PC9.Signal=GPIO_Output
PF0-OSC_IN.GPIOParameters=GPIO_Speed,PinState,GPIO_PuPd,GPIO_Label,GPIO_ModeDefaultOutputPP
PF0-OSC_IN.GPIO_Label=N_I2C_PU_EN_B
PF0-OSC_IN.GPIO_ModeDefaultOutputPP=GPIO_MODE_OUTPUT_PP
PF0-OSC_IN.GPIO_PuPd=GPIO_NOPULL
PF0-OSC_IN.GPIO_Speed=GPIO_SPEED_FREQ_LOW
PF0-OSC_IN.PinState=GPIO_PIN_SET
PF0-OSC_IN.Signal=GPIO_Output
PF1-OSC_OUT.GPIOParameters=GPIO_PuPd,GPIO_Label
PF1-OSC_OUT.GPIO_Label=N_VDD1_ERR
PF1-OSC_OUT.GPIO_PuPd=GPIO_PULLUP
PF1-OSC_OUT.Signal=GPIO_Input
PF6.GPIOParameters=GPIO_Speed,PinState,GPIO_PuPd,GPIO_Label,GPIO_ModeDefaultOutputPP
PF6.GPIO_Label=VDD1_SEL2
PF6.GPIO_ModeDefaultOutputPP=GPIO_MODE_OUTPUT_PP
PF6.GPIO_PuPd=GPIO_NOPULL
PF6.GPIO_Speed=GPIO_SPEED_FREQ_LOW
PF6.PinState=GPIO_PIN_RESET
PF6.Signal=GPIO_Output
PF7.GPIOParameters=GPIO_Speed,PinState,GPIO_PuPd,GPIO_Label,GPIO_ModeDefaultOutputPP
PF7.GPIO_Label=VDD1_SEL3
PF7.GPIO_ModeDefaultOutputPP=GPIO_MODE_OUTPUT_PP
PF7.GPIO_PuPd=GPIO_NOPULL
PF7.GPIO_Speed=GPIO_SPEED_FREQ_LOW
PF7.PinState=GPIO_PIN_RESET
PF7.Signal=GPIO_Output
RCC.SYSCLKFreq_VALUE=48000000
RCC.SYSCLKSource=RCC_SYSCLKSOURCE_PLLCLK
board=super_uart

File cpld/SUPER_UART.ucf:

#PACE: Start of Constraints generated by PACE

#PACE: Start of PACE I/O Pin Assignments
NET "CTS_A"  LOC = "P24" | SLEW = FAST ;
NET "CTS_B"  LOC = "P60" | SLEW = FAST ;
NET "DTR_A"  LOC = "P45" | SLEW = FAST ;
NET "DTR_B"  LOC = "P42" | SLEW = FAST ;
NET "FTDI_CTS_A"  LOC = "P11" | SLEW = FAST ;
NET "FTDI_CTS_B"  LOC = "P6" | SLEW = FAST ;
NET "FTDI_DTR_A"  LOC = "P10"  ;
NET "FTDI_DTR_B"  LOC = "P5"  ;
NET "FTDI_RTS_A"  LOC = "P15" | SLEW = FAST ;
NET "FTDI_RTS_B"  LOC = "P7" | SLEW = FAST ;
NET "FTDI_RXD_A"  LOC = "P16" | SLEW = FAST ;
NET "FTDI_RXD_B"  LOC = "P8" | SLEW = FAST ;
NET "FTDI_RXD_C"  LOC = "P2" | SLEW = FAST ;
NET "FTDI_RXD_D"  LOC = "P63" | SLEW = FAST ;
NET "FTDI_TXD_A"  LOC = "P17"  ;
NET "FTDI_TXD_B"  LOC = "P9"  ;
NET "TXD_C"  LOC = "P33"  ;
NET "FTDI_TXD_D"  LOC = "P64"  ;
NET "BUZZER"  LOC = "P19" | SLEW = FAST ;
NET "CPLD_OE"  LOC = "P43"  ;
NET "OPTO_EN"  LOC = "P20" | SLEW = FAST ;
NET "RXD_A"  LOC = "P25"  ;
NET "RXD_B"  LOC = "P48"  ;
NET "RXD_C"  LOC = "P44"  ;
NET "RXD_D"  LOC = "P61"  ;
NET "RXD_A_OC"  LOC = "P36" | SLEW = FAST ;
NET "RXD_B_OC"  LOC = "P49" | SLEW = FAST ;
NET "SR_CLK"  LOC = "P38"  ;
NET "SR_DATA"  LOC = "P50"  ;
NET "SR_LOAD"  LOC = "P39"  ;
NET "TXD_D"  LOC = "P62" | SLEW = FAST ;
NET "CTS_A_OC"  LOC = "P27" | SLEW = FAST ;
NET "CTS_B_OC"  LOC = "P57" | SLEW = FAST ;
NET "TXD_A"  LOC = "P35" | SLEW = FAST ;
NET "TXD_B"  LOC = "P56" | SLEW = FAST ;

#PACE: Start of PACE Area Constraints

#PACE: Start of PACE Prohibit Constraints

#PACE: End of Constraints generated by PACE

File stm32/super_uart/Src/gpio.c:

/**
  ******************************************************************************
  * File Name          : gpio.c
  * Description        : This file provides code for the configuration
  *                      of all used GPIO pins.
  ******************************************************************************
  ** This notice applies to any and all portions of this file
  * that are not between comment pairs USER CODE BEGIN and
  * USER CODE END. Other portions of this file, whether 
  * inserted by the user or by software development tools
  * are owned by their respective copyright owners.
  *
  * COPYRIGHT(c) 2017 STMicroelectronics
  *
  * Redistribution and use in source and binary forms, with or without modification,
  * are permitted provided that the following conditions are met:
  *   1. Redistributions of source code must retain the above copyright notice,
  *      this list of conditions and the following disclaimer.
  *   2. Redistributions in binary form must reproduce the above copyright notice,
  *      this list of conditions and the following disclaimer in the documentation
  *      and/or other materials provided with the distribution.
  *   3. Neither the name of STMicroelectronics nor the names of its contributors
  *      may be used to endorse or promote products derived from this software
  *      without specific prior written permission.
  *
  * THIS SOFTWARE IS PROVIDED BY THE COPYRIGHT HOLDERS AND CONTRIBUTORS "AS IS"
  * AND ANY EXPRESS OR IMPLIED WARRANTIES, INCLUDING, BUT NOT LIMITED TO, THE
  * IMPLIED WARRANTIES OF MERCHANTABILITY AND FITNESS FOR A PARTICULAR PURPOSE ARE
  * DISCLAIMED. IN NO EVENT SHALL THE COPYRIGHT HOLDER OR CONTRIBUTORS BE LIABLE
  * FOR ANY DIRECT, INDIRECT, INCIDENTAL, SPECIAL, EXEMPLARY, OR CONSEQUENTIAL
  * DAMAGES (INCLUDING, BUT NOT LIMITED TO, PROCUREMENT OF SUBSTITUTE GOODS OR
  * SERVICES; LOSS OF USE, DATA, OR PROFITS; OR BUSINESS INTERRUPTION) HOWEVER
  * CAUSED AND ON ANY THEORY OF LIABILITY, WHETHER IN CONTRACT, STRICT LIABILITY,
  * OR TORT (INCLUDING NEGLIGENCE OR OTHERWISE) ARISING IN ANY WAY OUT OF THE USE
  * OF THIS SOFTWARE, EVEN IF ADVISED OF THE POSSIBILITY OF SUCH DAMAGE.
  *
  ******************************************************************************
  */

/* Includes ------------------------------------------------------------------*/
#include "gpio.h"
/* USER CODE BEGIN 0 */

/* USER CODE END 0 */

/*----------------------------------------------------------------------------*/
/* Configure GPIO                                                             */
/*----------------------------------------------------------------------------*/
/* USER CODE BEGIN 1 */

/* USER CODE END 1 */

/** Configure pins as 
        * Analog 
        * Input 
        * Output
        * EVENT_OUT
        * EXTI
        * Free pins are configured automatically as Analog (this feature is enabled through 
        * the Code Generation settings)
*/
void MX_GPIO_Init(void)
{

  GPIO_InitTypeDef GPIO_InitStruct;

  /* GPIO Ports Clock Enable */
  __HAL_RCC_GPIOC_CLK_ENABLE();
  __HAL_RCC_GPIOF_CLK_ENABLE();
  __HAL_RCC_GPIOA_CLK_ENABLE();
  __HAL_RCC_GPIOB_CLK_ENABLE();
  __HAL_RCC_GPIOD_CLK_ENABLE();

  /*Configure GPIO pin Output Level */
  HAL_GPIO_WritePin(GPIOC, COL2_Pin|CPLD_OE_Pin|COL3_Pin|COL4_Pin 
                          |N_I2C_PU_EN_A_Pin, GPIO_PIN_SET);

  /*Configure GPIO pin Output Level */
  HAL_GPIO_WritePin(N_I2C_PU_EN_B_GPIO_Port, N_I2C_PU_EN_B_Pin, GPIO_PIN_SET);

  /*Configure GPIO pin Output Level */
  HAL_GPIO_WritePin(GPIOC, SPI_EN_B_Pin|VDD2_SEL3_Pin, GPIO_PIN_RESET);

  /*Configure GPIO pin Output Level */
  HAL_GPIO_WritePin(GPIOA, N_VDD1_EN_Pin|N_FTDI_RESET_Pin|TXD_Pin, GPIO_PIN_SET);

  /*Configure GPIO pin Output Level */
  HAL_GPIO_WritePin(GPIOA, LED1_Pin|LED2_Pin|LED5_Pin, GPIO_PIN_RESET);

  /*Configure GPIO pin Output Level */
  HAL_GPIO_WritePin(GPIOB, LED3_Pin|LED4_Pin|SR_LOAD_Pin|VDD2_SEL2_Pin 
                          |SPI_EN_A_Pin, GPIO_PIN_RESET);

  /*Configure GPIO pin Output Level */
  HAL_GPIO_WritePin(GPIOB, N_ENUMERATE_Pin|N_VDD2_EN_Pin|COL1_Pin, GPIO_PIN_SET);

  /*Configure GPIO pin Output Level */
  HAL_GPIO_WritePin(GPIOF, VDD1_SEL2_Pin|VDD1_SEL3_Pin, GPIO_PIN_RESET);

  /*Configure GPIO pins : PCPin PCPin PCPin PCPin */
  GPIO_InitStruct.Pin = N_PWREN_Pin|SW2_Pin|N_USB_SUSPEND_Pin|SW1_Pin;
  GPIO_InitStruct.Mode = GPIO_MODE_INPUT;
  GPIO_InitStruct.Pull = GPIO_PULLUP;
  HAL_GPIO_Init(GPIOC, &GPIO_InitStruct);

  /*Configure GPIO pins : PC14 PC5 PC6 PC10 
                           PC11 */
  GPIO_InitStruct.Pin = GPIO_PIN_14|GPIO_PIN_5|GPIO_PIN_6|GPIO_PIN_10 
                          |GPIO_PIN_11;
  GPIO_InitStruct.Mode = GPIO_MODE_ANALOG;
  GPIO_InitStruct.Pull = GPIO_NOPULL;
  HAL_GPIO_Init(GPIOC, &GPIO_InitStruct);

  /*Configure GPIO pins : PCPin PCPin PCPin PCPin 
                           PCPin PCPin PCPin */
  GPIO_InitStruct.Pin = COL2_Pin|CPLD_OE_Pin|SPI_EN_B_Pin|COL3_Pin 
                          |COL4_Pin|N_I2C_PU_EN_A_Pin|VDD2_SEL3_Pin;
  GPIO_InitStruct.Mode = GPIO_MODE_OUTPUT_PP;
  GPIO_InitStruct.Pull = GPIO_NOPULL;
  GPIO_InitStruct.Speed = GPIO_SPEED_FREQ_LOW;
  HAL_GPIO_Init(GPIOC, &GPIO_InitStruct);

  /*Configure GPIO pins : PFPin PFPin PFPin */
  GPIO_InitStruct.Pin = N_I2C_PU_EN_B_Pin|VDD1_SEL2_Pin|VDD1_SEL3_Pin;
  GPIO_InitStruct.Mode = GPIO_MODE_OUTPUT_PP;
  GPIO_InitStruct.Pull = GPIO_NOPULL;
  GPIO_InitStruct.Speed = GPIO_SPEED_FREQ_LOW;
  HAL_GPIO_Init(GPIOF, &GPIO_InitStruct);

  /*Configure GPIO pin : PtPin */
  GPIO_InitStruct.Pin = N_VDD1_ERR_Pin;
  GPIO_InitStruct.Mode = GPIO_MODE_INPUT;
  GPIO_InitStruct.Pull = GPIO_PULLUP;
  HAL_GPIO_Init(N_VDD1_ERR_GPIO_Port, &GPIO_InitStruct);

  /*Configure GPIO pins : PAPin PAPin PAPin PAPin 
                           PAPin PAPin */
  GPIO_InitStruct.Pin = N_VDD1_EN_Pin|N_FTDI_RESET_Pin|LED1_Pin|LED2_Pin 
                          |LED5_Pin|TXD_Pin;
  GPIO_InitStruct.Mode = GPIO_MODE_OUTPUT_PP;
  GPIO_InitStruct.Pull = GPIO_NOPULL;
  GPIO_InitStruct.Speed = GPIO_SPEED_FREQ_LOW;
  HAL_GPIO_Init(GPIOA, &GPIO_InitStruct);

  /*Configure GPIO pins : PAPin PAPin PAPin */
  GPIO_InitStruct.Pin = SW3_Pin|RXD_Pin|SW4_Pin;
  GPIO_InitStruct.Mode = GPIO_MODE_INPUT;
  GPIO_InitStruct.Pull = GPIO_PULLUP;
  HAL_GPIO_Init(GPIOA, &GPIO_InitStruct);

  /*Configure GPIO pins : PA3 PA4 PA5 PA15 */
  GPIO_InitStruct.Pin = GPIO_PIN_3|GPIO_PIN_4|GPIO_PIN_5|GPIO_PIN_15;
  GPIO_InitStruct.Mode = GPIO_MODE_ANALOG;
  GPIO_InitStruct.Pull = GPIO_NOPULL;
  HAL_GPIO_Init(GPIOA, &GPIO_InitStruct);

  /*Configure GPIO pins : PF4 PF5 */
  GPIO_InitStruct.Pin = GPIO_PIN_4|GPIO_PIN_5;
  GPIO_InitStruct.Mode = GPIO_MODE_ANALOG;
  GPIO_InitStruct.Pull = GPIO_NOPULL;
  HAL_GPIO_Init(GPIOF, &GPIO_InitStruct);

  /*Configure GPIO pins : PBPin PBPin PBPin PBPin 
                           PBPin PBPin PBPin PBPin */
  GPIO_InitStruct.Pin = LED3_Pin|LED4_Pin|N_ENUMERATE_Pin|SR_LOAD_Pin 
                          |VDD2_SEL2_Pin|SPI_EN_A_Pin|N_VDD2_EN_Pin|COL1_Pin;
  GPIO_InitStruct.Mode = GPIO_MODE_OUTPUT_PP;
  GPIO_InitStruct.Pull = GPIO_NOPULL;
  GPIO_InitStruct.Speed = GPIO_SPEED_FREQ_LOW;
  HAL_GPIO_Init(GPIOB, &GPIO_InitStruct);

  /*Configure GPIO pins : PB2 PB11 PB14 PB9 */
  GPIO_InitStruct.Pin = GPIO_PIN_2|GPIO_PIN_11|GPIO_PIN_14|GPIO_PIN_9;
  GPIO_InitStruct.Mode = GPIO_MODE_ANALOG;
  GPIO_InitStruct.Pull = GPIO_NOPULL;
  HAL_GPIO_Init(GPIOB, &GPIO_InitStruct);

  /*Configure GPIO pin : PD2 */
  GPIO_InitStruct.Pin = GPIO_PIN_2;
  GPIO_InitStruct.Mode = GPIO_MODE_ANALOG;
  GPIO_InitStruct.Pull = GPIO_NOPULL;
  HAL_GPIO_Init(GPIOD, &GPIO_InitStruct);

  /*Configure GPIO pin : PtPin */
  GPIO_InitStruct.Pin = N_VDD2_ERR_Pin;
  GPIO_InitStruct.Mode = GPIO_MODE_INPUT;
  GPIO_InitStruct.Pull = GPIO_PULLUP;
  HAL_GPIO_Init(N_VDD2_ERR_GPIO_Port, &GPIO_InitStruct);

}

/* USER CODE BEGIN 2 */

/* USER CODE END 2 */

/**
  * @}
  */

/**
  * @}
  */

/************************ (C) COPYRIGHT STMicroelectronics *****END OF FILE****/

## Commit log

2017-06-03 Working on schematic
2017-06-18 PCB placement
2017-07-09 Routing before moving to 4 layers
2017-07-15 Front board routed
2017-07-15 Silkscreen and 3D model updated
2017-10-21 Add CPLD project
2017-11-04 STM32 firmware - initial commit
2020-11-18 Add missing files
